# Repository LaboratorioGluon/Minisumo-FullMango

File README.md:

# 🤖 Robot 🤖 Minisumo FullMango

Mi robot de competición para la OSHWDEM 2026, el minisumo :tangerine: **FullMango** :tangerine:  (Perdón, no había emoji de un mango).

Hecho 100% en directos de Twitch y Youtube, desde las pruebas de concepto, la electrónica con PCB y la programación del microcontrolador de ST.
-   Twitch: [www.twitch.tv/labgluon](https://www.twitch.tv/labgluon)
-   Youtube: [www.youtube.com/labgoratoriogluon](www.youtube.com/labgoratoriogluon)

# :wrench: Componentes Principales :wrench:
- **PCB** : Diseño propio hecho en KiCAD, proyecto en carpeta `Schematics/MinisumoV2/`
- **Estructura:** Para añadir peso y consistencia esta basado en placas perforadas de acero cincado.
    - Diseño 3D alrededor de estas piezas hecho en OnShape (carpeta `3D').
- **Motores**: De maquina de tatuaje, coreless (Modelo M2610, Ref: [Aliexpress](https://es.aliexpress.com/item/4001010632280.html?spm=a2g0o.order_detail.order_detail_item.3.169258bfselo3b&gatewayAdapt=glo2esp))
- **Electrónica**:
    - *Procesador*: **STM32H523CCT6**
    - *Driver motores*: **MP6551**
    - *Sensor de línea*: **QRE1113** (Ref: [Aliexpress](https://s.click.aliexpress.com/e/_c4XDYlMh))
    - *Senor de enemigo*:  **GP2Y0E03** (Ref [Aliexpress](https://s.click.aliexpress.com/e/_c443dXyh))
    - *Alimentación* :
        - Batería 3S Tattu 550 mAh
        - Regulador switching: **TPS563201**
        - Regulador lineal: **AMS1117-3.3**

# :computer: Sobre el Software :computer:

El robot minisumo FullMango se basa en un control por máquina de estados. Siendo los 3 principales:
- **Wait RC5** (`start_state` en el código): Una vez que el Robot se ha inicializado correctamente espera a la señal del **mando RC5**
- **Seek** (`seek_state`): Es el patrón de búsqueda hasta encontrar al enemigo.
- **Attack** (`fight_state`): Cuando el robot ya ha encontrado al enemigo y va a por él.

## Control de motores

Para el control de motores se ha implementado una doble rampa de cara a intentar resolver el problema de los caballitos: los motores son muy potentes y si pasamos al 80% de golpe, el **robot se da la vuelta**.

# Configuracion

| Pin     | Function |
| ------- | -------- |
| Ninguno | FWD      |
| 1       | RIGHT    |
| 2       | LEFT     |
| 3       | BACK     |

# Otros enlaces

- [Pagina Web (Castellano)](https://www.laboratoriogluon.com/)
- [Webpage (English)](https://en.laboratoriogluon.com/)

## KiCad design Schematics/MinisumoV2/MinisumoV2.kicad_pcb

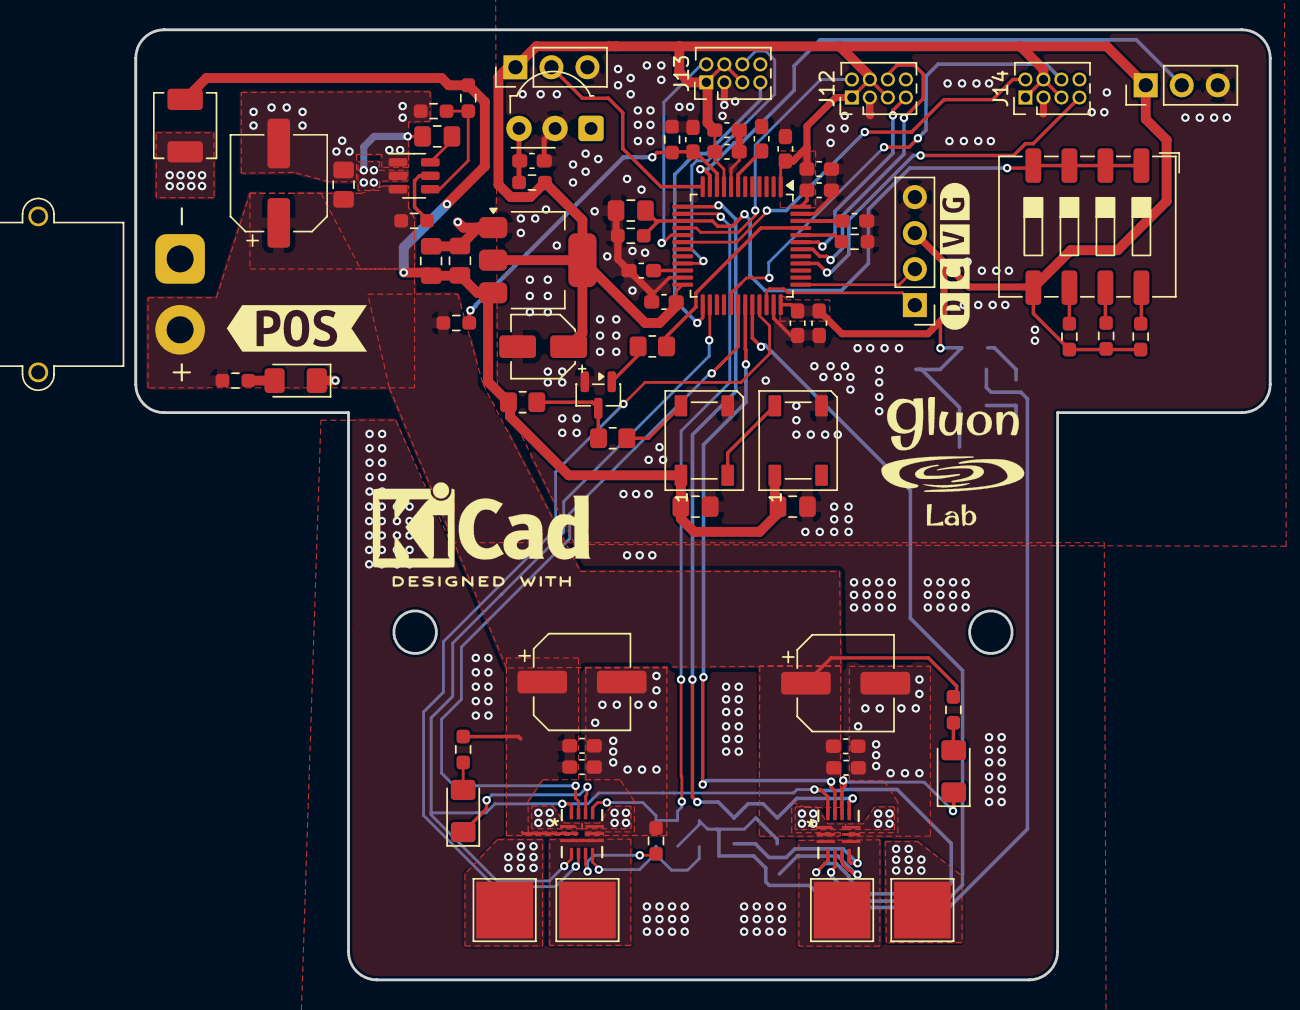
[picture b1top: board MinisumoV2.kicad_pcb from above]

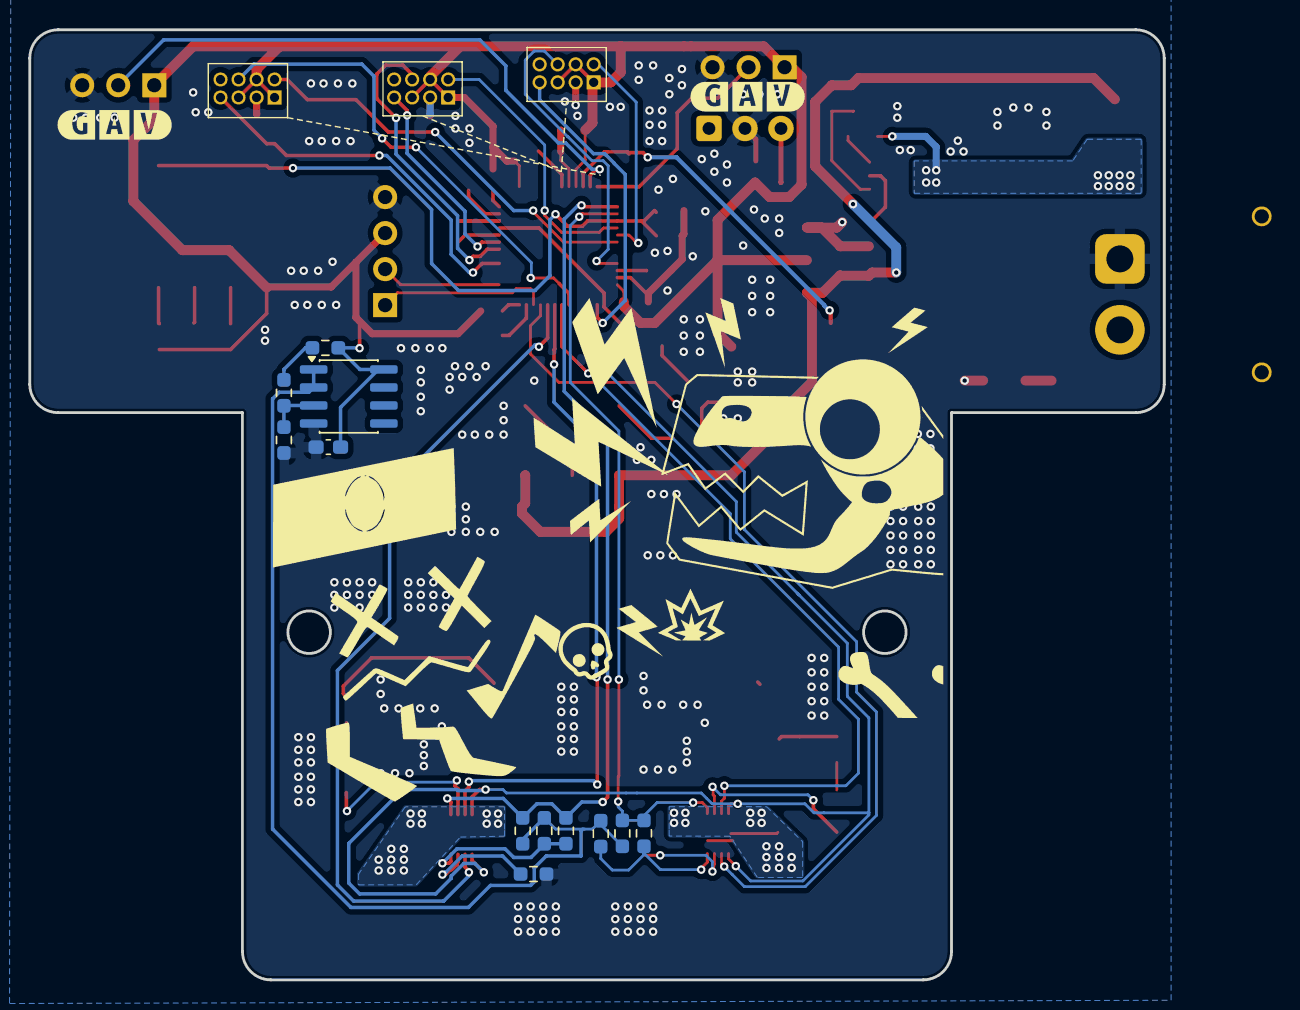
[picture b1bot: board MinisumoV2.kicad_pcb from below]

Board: 2 copper layers, 80.0 x 67.0 mm, 87 parts (14 on the bottom side), 59 nets.

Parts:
C1, C10: 1u; C_0603_1608Metric_Pad1.08x0.95mm_HandSolder
C2, C4, C7, C8, C9, C11, C20, C22, C24: 100n; C_0603_1608Metric_Pad1.08x0.95mm_HandSolder
C3: 4u7; C_0603_1608Metric_Pad1.08x0.95mm_HandSolder
C5, C6, C27: 2u2; C_0603_1608Metric_Pad1.08x0.95mm_HandSolder
C12, C28, C29: 100nF; C_0805_2012Metric_Pad1.18x1.45mm_HandSolder
C13: 22u; C_0603_1608Metric_Pad1.08x0.95mm_HandSolder
C14: 100u; CP_Elec_6.3x5.4
C15, C17, C18: 22u; C_0805_2012Metric_Pad1.18x1.45mm_HandSolder
C16: 100n; C_0805_2012Metric_Pad1.18x1.45mm_HandSolder
C19: C_Polarized_US; CP_Elec_4x5.3
C21, C25: 10u; C_0603_1608Metric_Pad1.08x0.95mm_HandSolder
C23, C26: 470u; CP_Elec_6.3x5.4
D1: FaultL; LED_1206_3216Metric_Pad1.42x1.75mm_HandSolder
D2: FaultR; LED_1206_3216Metric_Pad1.42x1.75mm_HandSolder
D3: vBatt; LED_1206_3216Metric_Pad1.42x1.75mm_HandSolder
D4, D5: WS2812B; LED_WS2812B_PLCC4_5.0x5.0mm_P3.2mm
J1: SWD_CONNECTOR; PinHeader_1x04_P2.54mm_Vertical
J2: BATT; AMASS_XT30PW-M_1x02_P2.50mm_Horizontal
J3: MOTOR_L_1; TestPoint_Pad_4.0x4.0mm
J4: MOTOR_L_2; TestPoint_Pad_4.0x4.0mm
J5: MOTOR_R_1; TestPoint_Pad_4.0x4.0mm
J6: MOTOR_R_2; TestPoint_Pad_4.0x4.0mm
J10: LINE_RIGHT; PinHeader_1x03_P2.54mm_Vertical
J11: LINE_LEFT; PinHeader_1x03_P2.54mm_Vertical
J12: SHARP_CENTER; PinHeader_2x04_P1.27mm_Vertical
J13: SHARP_LEFT; PinHeader_2x04_P1.27mm_Vertical
J14: SHARP_RIGHT; PinHeader_2x04_P1.27mm_Vertical
L1: 3u3; L_Sunlord_MWSA0412S
Q4: IRLML2502; SOT-23
R1, R10, R11, R12, R15, R16, R17, R19, R20, R21, R23, R24: 10k; R_0603_1608Metric_Pad0.98x0.95mm_HandSolder
R2, R3, R7, R8: 4k7; R_0603_1608Metric_Pad0.98x0.95mm_HandSolder
R4, R5, R14: 2k2; R_0603_1608Metric_Pad0.98x0.95mm_HandSolder
R6: 1k; R_0603_1608Metric_Pad0.98x0.95mm_HandSolder
R9: 47k; R_0603_1608Metric_Pad0.98x0.95mm_HandSolder
R13: 54k9; R_0603_1608Metric_Pad0.98x0.95mm_HandSolder
R18, R22: 0; R_0603_1608Metric_Pad0.98x0.95mm_HandSolder
R25: 47; R_0603_1608Metric_Pad0.98x0.95mm_HandSolder
R26: 470; R_0805_2012Metric_Pad1.20x1.40mm_HandSolder
R27: 10k; R_0805_2012Metric_Pad1.20x1.40mm_HandSolder
R28: 100; R_0805_2012Metric_Pad1.20x1.40mm_HandSolder
SW1: SW_DIP_x04; SW_DIP_SPSTx04_Slide_9.78x12.34mm_W8.61mm_P2.54mm
U1: STM32H523CCTx; LQFP-48_7x7mm_P0.5mm
U2: TPS563201; SOT-23-6
U3: AMS1117-3.3; SOT-223-3_TabPin2
U4: LM358; SOIC-8_3.9x4.9mm_P1.27mm
U5, U6: MP6551; QFN-14_MP6551_MNP
U7: IRM-56384; Vishay_MOLD-3Pin
kibuzzard-69A73CC0: G***; kibuzzard-69A73CC0
kibuzzard-69A732F2: G***; kibuzzard-69A732F2
kibuzzard-69A73765: G***; kibuzzard-69A73765
kibuzzard-69A73775: G***; kibuzzard-69A73775

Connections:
+3V3: C1.1, C3.1, C4.1, C7.1, C8.1, C9.1, C10.1, C11.1, C19.1, C22.1, J1.3, J10.1, J11.1, J12.1, J12.4, J12.5, J13.1, J13.4, J13.5, J14.1, J14.4, J14.5, R2.2, R4.2, R6.2, R14.2, R25.1, SW1.5, U1.1 (VBAT), U1.9 (VDDA), U1.24 (VDD), U1.36 (VDD), U1.48 (VDD), U3.2 (VO), U4.8 (V+)
+5V: C17.1, C18.1, C28.1, C29.1, D4.1 (VDD), D5.1 (VDD), L1.2, R13.2, R27.1, U3.3 (VI)
/CONFIG_ADC: C12.1, R5.2, SW1.1, SW1.2, SW1.3, SW1.4, U1.15 (PA5)
/LEDS_WS: R28.1, U1.45 (PB8)
/LINE_LEFT: J11.2, U1.12 (PA2)
/LINE_RIGHT: J10.2, U1.11 (PA1)
/MOTOR_ENABLE: U1.26 (PB13), U5.4 (EN2), U5.14 (EN1), U6.4 (EN2), U6.14 (EN1)
/Motors/MOTOR_L.IN1: U1.30 (PA9), U5.13 (IN1)
/Motors/MOTOR_L.IN2: U1.33 (PA12), U5.5 (IN2)
/Motors/MOTOR_L_FAULT: D1.1 (K), U5.12 (~FAULT)
/Motors/MOTOR_R.IN1: U1.31 (PA10), U6.13 (IN1)
/Motors/MOTOR_R.IN2: U1.32 (PA11), U6.5 (IN2)
/Motors/MOTOR_R_FAULT: D2.1 (K), U6.12 (~FAULT)
/Motors/MOTOR_SENSE_L: R17.2, R18.2, U1.14 (PA4), U5.11 (CM1)
/Motors/MOTOR_SENSE_R: R21.2, R22.2, U1.13 (PA3), U6.11 (CM1)
/Motors/MOTOR_V_REF: R17.1, R19.1, R21.1, R23.1, U4.1, U4.2 (-)
/Motors/m_l_1: J3.1, U5.1 (OUT1), U5.10 (OUT1)
/Motors/m_l_2: J4.1, U5.3 (OUT2), U5.8 (OUT2)
/Motors/m_r_1: J5.1, U6.1 (OUT1), U6.10 (OUT1)
/Motors/m_r_2: J6.1, U6.3 (OUT2), U6.8 (OUT2)
/SHARP_C_ANALOG: J12.2, U1.16 (PA6)
/SHARP_C_SCL: J12.6, U1.42 (PB6)
/SHARP_C_SDA: J12.7, U1.43 (PB7)
/SHARP_L_ANALOG: J13.2, U1.17 (PA7)
/SHARP_L_SCL: J13.6, U1.21 (PB10)
/SHARP_L_SDA: J13.7, U1.25 (PB12)
/SHARP_R_ANALOG: J14.2, U1.18 (PB0)
/SHARP_R_SCL: J14.6, U1.29 (PA8)
/SHARP_R_SDA: J14.7, U1.40 (PB4(NJTRST))
/SWCLK: J1.2, U1.37 (PA14(JTCK)
/SWDIO: J1.1, U1.34 (PA13(JTMS)
/V_BATT: C14.1, C15.1, C20.1, C21.1, C23.1, C24.1, C25.1, C26.1, J2.2, R3.1, R7.1, R8.1, R9.1, R11.2, U2.3 (VIN), U5.2 (VIN), U6.2 (VIN)
/V_BATT_SENSE: C13.1, R9.2, R10.1, U1.10 (PA0)
GND: C1.2, C2.2, C3.2, C4.2, C5.2, C6.2, C7.2, C8.2, C9.2, C10.2, C11.2, C12.2, C13.2, C14.2, C15.2, C17.2, C18.2, C19.2, C20.2, C21.2, C22.2, C23.2, C24.2, C25.2, C26.2, C27.2, C28.2, C29.2, D3.1 (K), D4.3 (VSS), D5.3 (VSS), J1.4, J2.1, J10.3, J11.3, J12.3, J13.3, J14.3, Q4.2 (S), R1.1, R5.1, R10.2, R12.2, R16.1, R20.1, R24.1, U1.8 (VSSA), U1.23 (VSS), U1.35 (VSS), U1.47 (VSS), U2.1 (GND), U3.1 (GND), U4.4 (V-), U5.9 (GND), U6.9 (GND), U7.2 (GND)
unnamed: C5.1, U1.22 (VCAP)
unnamed: C6.1, U1.46 (VCAP)
unnamed: D1.2 (A), R3.2
unnamed: D2.2 (A), R7.2
unnamed: D3.2 (A), R8.2
unnamed: D4.4 (DIN), R26.1
unnamed: D4.2 (DOUT), D5.4 (DIN)
unnamed: Q4.3 (D), R26.2, R27.2
unnamed: Q4.1 (G), R28.2
unnamed: R2.1, SW1.8
unnamed: R4.1, SW1.7
unnamed: R6.1, SW1.6
unnamed: R14.1, R15.2
unnamed: R1.2, U1.44 (BOOT0)
unnamed: C2.1, U1.7 (NRST)
unnamed: R11.1, U2.5 (EN)
unnamed: C16.2, L1.1, U2.2 (SW)
unnamed: C16.1, U2.6 (VBST)
unnamed: R12.1, R13.1, U2.4 (VFB)
unnamed: R15.1, R16.2, U4.3 (+)
unnamed: R18.1, R19.2, U5.7 (CM2)
unnamed: R20.2, U5.6 (SR)
unnamed: R22.1, R23.2, U6.7 (CM2)
unnamed: R24.2, U6.6 (SR)
unnamed: C27.1, R25.2, U7.3 (Vs)

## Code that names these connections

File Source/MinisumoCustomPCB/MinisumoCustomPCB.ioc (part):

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Mcu.Name=STM32H523CCTx
Mcu.Package=LQFP48
Mcu.UserName=STM32H523CCTx
PA0.GPIOParameters=GPIO_Label
PA0.GPIO_Label=V_BATT_SENSE
PA0.Signal=ADCx_INP0
PA1.GPIOParameters=GPIO_Label
PA1.GPIO_Label=LINE_RIGHT
PA1.Signal=ADCx_INP1
PA10.Signal=S_TIM1_CH3
PA11.Signal=GPIO_Output
PA12.Signal=GPIO_Output
PA2.GPIOParameters=GPIO_Label
PA2.GPIO_Label=LINE_LEFT
PA2.Signal=ADCx_INP14
PA3.GPIOParameters=GPIO_Label
PA3.GPIO_Label=MOTOR_SENSE_R
PA3.Signal=ADCx_INP15
PA4.GPIOParameters=GPIO_Label
PA4.GPIO_Label=MOTOR_SENSE_L
PA4.Signal=ADCx_INP18
PA5.GPIOParameters=GPIO_Label
PA5.GPIO_Label=CONFIG_ADC
PA5.Signal=ADCx_INP19
PA6.GPIOParameters=GPIO_Label
PA6.GPIO_Label=SHARP_C_ANALOG
PA6.Signal=ADCx_INP3
PA7.GPIOParameters=GPIO_Label
PA7.GPIO_Label=SHARP_L_ANALOG
PA7.Signal=ADCx_INP7
PA9.Signal=S_TIM1_CH2
PB0.GPIOParameters=GPIO_Label
PB0.GPIO_Label=SHARP_R_ANALOG
PB0.Signal=ADCx_INP9
PB1.GPIOParameters=GPIO_ModeDefaultEXTI
PB1.GPIO_ModeDefaultEXTI=GPIO_MODE_IT_RISING_FALLING
PB1.Signal=GPXTI1
PB13.GPIOParameters=GPIO_Label
PB13.GPIO_Label=MOTOR_ENABLE
PB13.Signal=GPIO_Output
PB5.Mode=Asynchronous
PB5.Signal=UART5_RX
PB6.Mode=Asynchronous
PB6.Signal=UART5_TX
PB8.Signal=S_TIM4_CH3
RCC.HSE_VALUE=25000000
RCC.SYSCLKFreq_VALUE=250000000
RCC.SYSCLKSource=RCC_SYSCLKSOURCE_PLLCLK
board=custom
